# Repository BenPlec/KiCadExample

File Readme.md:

# <font color="#DCB033">KiCad 교육자료</font>

> 작성자: 김병헌   
> release date: 2025년 03월 24일    

- 본 Repository는 Academy 교육 목적으로 만들어진 샘플 PCB 예제로써, 공식 권한을 갖는 자료가 아닙니다.
- PLECKO의 Academy 지원 규정에 따라 학교/연구소를 대상으로 교육 후 제한적인 상담이 가능합니다.
- [<i>예제 설명</i>](/PT_01C_KiCad%20Example_v1.1.pdf)

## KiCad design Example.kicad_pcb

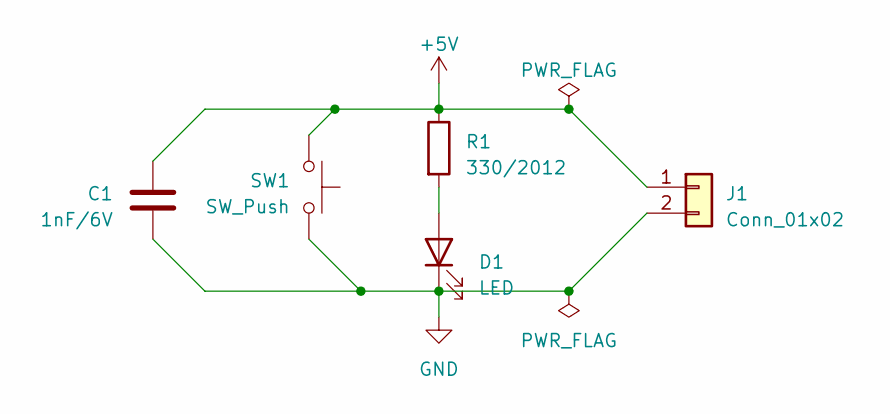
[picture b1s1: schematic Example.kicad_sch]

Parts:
C1: 1nF/6V; C_0805_2012Metric_Pad1.18x1.45mm_HandSolder
D1: LED; LED_0805_2012Metric_Pad1.15x1.40mm_HandSolder
J1: Conn_01x02; PinHeader_1x02_P2.54mm_Vertical
R1: 330/2012; R_0805_2012Metric_Pad1.20x1.40mm_HandSolder
SW1: SW_Push; SW_Push_1P1T_NO_CK_KSC6xxJ

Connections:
+5V: C1.1, J1.1, R1.1, SW1.2
GND: C1.2, D1.1 (K), J1.2, SW1.1
unnamed: D1.2 (A), R1.2

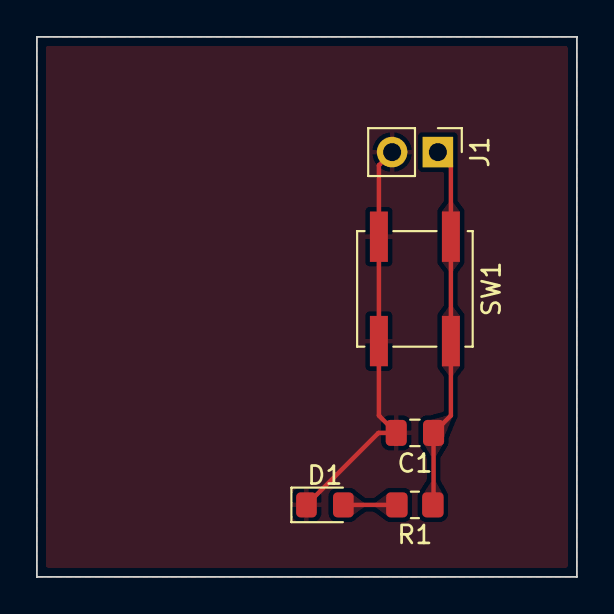
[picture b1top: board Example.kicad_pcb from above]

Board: 2 copper layers, 30.0 x 30.0 mm, 5 parts (0 on the bottom side), 3 nets.

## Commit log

2024-04-06 <Start> Sample project
2024-04-06 <Major> Add presentation PDF file
2024-04-06 <minor> Add cleanup and teardrop ex
2025-03-24 2025 1Q Update
2025-03-24 add readMe
